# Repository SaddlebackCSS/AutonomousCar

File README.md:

# Autonomous Car for Sparkfun AVC

---
Will post more later once finals are over but I wanted to start the repo. Most information will go in the wiki, since there is a lot of  specialized terms and knowledge to the RC world. People who want to help should have a centeralized place to go to learn what they need so that this project is less intimidating to people with no prior knowledge of RC or robotics.
</br> [Read about last years contest](avc.sparkfun.com/2015)
</br> [Some pictures and info from last year on HackaDay](hackaday.io/project/6404/logs)
</br> [Video recap of last year on youtube](www.youtube.com/watch?v=tZ3fpZFWHDM)
</br> [Youtube preview of last years course, for an idea of whats involved](www.youtube.com/watch?v=ZOcVDljZUFs)

#### What we can learn from this project:
  * Microcontroller programming (aruindo, etc)
  * Embedded Computers (single board computers like the pi)
  * Signals and Controls
  * Sensor Fusion
  * Hardware design and prototyping
  * Assembly Language - I don't know it but if you do then its a great opportunity to flex your knowledge!
  * AI - probably very crude but we can see
  * Computer Vision - maybe out of reach for this first year but would be awesome!
  * Working as a team and using real life engineering best practices (!)
  * An awesome trip to the competition for those who can make it!

#### Needed Knowledge (future wiki topics):
* Electrical Subsystems of a RC vehicle
  * Lipo Battery
  * Electronic Speed Controller
  * Servo
  * Receiver (or in our case a computer/microcontroller)
  * Electric Motor
    * Brushed electric motors
    * Brushless Electric Motors
  * Signals and Controls
    * Analog vs Digital
    * Pulse Width Modulations
    * I2C serial
    * SPI serial
    * Closed Loop Feedback

Obviously what you learn is really up to what you are interested in. If you could care less about hardware but want to jsut play with computer vision or someother navigation method then thats ok! If we want we could even make more than one car, and there is also a battle bot competition if some people are more interested in that.

# Find IP of beaglebone on Windows at Saddleback
- Open CMD
- Type "nslookup beaglebone". The output will look something like: 

```
Server:  dns1.saddleback.edu
Address:  10.151.253.251

Non-authoritative answer:
Name:  beaglebone.saddleback.edu
Address:  10.151.12.96
```

- Use the address associated with beaglebone.saddleback.edu with ssh on Linux/OSX or in PUTTY(installed on school computers already)

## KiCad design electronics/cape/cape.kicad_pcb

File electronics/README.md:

# Electronics Design Files

---
This folder contains design files for harware, both schematics and layout files. the were created with the open-source program [KiCad](http://kicad-pcb.org/) which is a product of FERMI labs.

</br> [Download KiCad for windows](kicad-pcb.org/download/windows/) - Also in the AUR and most linux repositories!
</br> [Contexual Electronics - Very Good YouTUbe chan with KiCad tutorials](www.youtube.com/user/contextualelectronic/playlists)
</br> [Octopart Part Finder & price Comparison](octopart.com/)
</br> [Digikey Parts Supplier](www.digikey.com)
</br> [Mouser Parts Supply](www.mouser.com/)
</br> [PCB Fabrication Price Comparison](pcbshopper.com/)

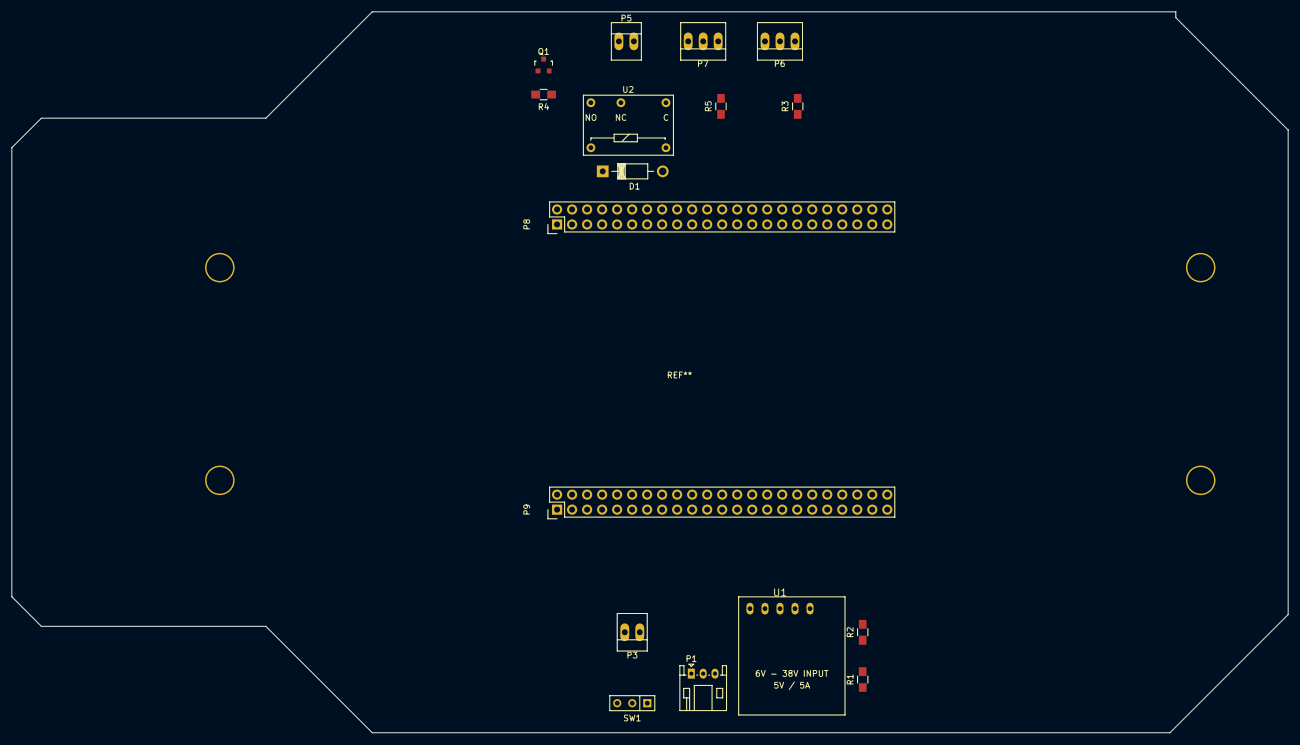
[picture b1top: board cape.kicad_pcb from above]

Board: 2 copper layers, 216.0 x 122.0 mm, 17 parts (0 on the bottom side), 16 nets, no tracks yet.

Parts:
D1: D; Diode_DO-41_SOD81_Horizontal_RM10
P1: CONN_01X03; JST_PH_S3B-PH-K_03x2.00mm_Angled
P3, P5: CONN_01X02; PINHEAD1-2
P6, P7: CONN_01X03; PINHEAD1-3
P8, P9: BeagleBone_Black_Header; Socket_BeagleBone_Black
Q1: BSS138; SOT-23
R1, R2, R5: R; R_0805_HandSoldering
R3: 1k; R_0805_HandSoldering
R4: 100k; R_0805_HandSoldering
SW1: SWITCH_INV; SW_Micro_SPST
U1: D24V50F5
U2: OMRON_RELAY_G6E; Relay_SPDS_OMRON-G6E

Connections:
+3V3: P6.2, P9.3, P9.4
+5V: D1.1, P9.5, P9.6, U2.1
ESC_SWITCH: Q1.1, R4.2
GNDD: P6.3, P7.3, P8.1, P8.2, P9.1, P9.2, P9.43, P9.44, P9.45, P9.46, Q1.2, R4.1
unnamed: D1.2, Q1.3, U2.6
unnamed: P1.1, SW1.2
unnamed: P1.3, R1.1
unnamed: P3.1, U1.3, U1.4
unnamed: P3.2, U1.5
unnamed: P5.1, U2.12
unnamed: P5.2, U2.7
unnamed: P6.1, R3.1
unnamed: P7.1, R5.2
unnamed: R1.2, R2.1, U1.1
unnamed: R2.2, SW1.3, U1.2
SYS_5V: P9.7, P9.8

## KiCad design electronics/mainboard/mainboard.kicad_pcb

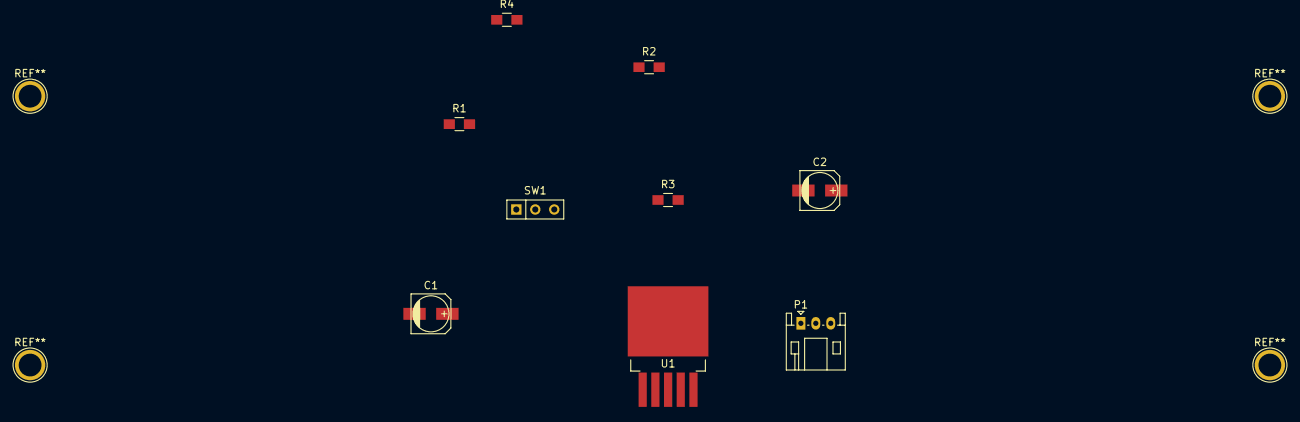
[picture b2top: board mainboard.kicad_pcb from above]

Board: 2 copper layers, 9 parts (0 on the bottom side), 6 nets, no tracks yet.

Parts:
C1: 10uF; c_elec_5x5.3
C2: 22uF; c_elec_5x5.3
P1: CONN_01X03; JST_PH_S3B-PH-K_03x2.00mm_Angled
R1, R2: 100K; R_0805_HandSoldering
R3: 33K; R_0805_HandSoldering
R4: 15K; R_0805_HandSoldering
SW1: SWITCH_INV; SW_Micro_SPST
U1: MIC29312; TO-263-5Lead

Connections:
/power supply/5V: C2.1, R2.1, U1.4
GND: C1.2, C2.2, P1.3, R3.2, R4.1, U1.3
unnamed: C1.1, R1.2, SW1.3, U1.2
unnamed: P1.1, SW1.2
unnamed: R1.1, R4.2, U1.1
unnamed: R2.2, R3.1, U1.5

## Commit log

2015-03-01 work from todays meeting
2015-03-01 Working on overlay files
2015-12-23 updated ignore file
2015-12-23 Servo/Controls Test Program
2015-12-23 started work on ESC control lib
2016-02-02 First Commit New Page
2016-02-02 config update
2016-02-02 updated about
2016-02-02 updated ignore and added images
2016-02-02 background image edited in css
2016-02-02 changed markdown to karmdown
2016-02-02 updated page titles
2016-02-02 changes to rouge for highlighting
2016-02-04 changed to platformIO and clion build env
2016-02-04 clion files
2016-02-10 cleared example posts and added post
2016-02-12 starting new blog entry
2016-02-12 working on post
2016-02-12 working
2016-03-06 add waffle.io badge
2016-04-01 add libraries for GPIO and PWM pin control
2016-04-01 add overlay for steering and script for compiling it
2016-04-01 rename steering overlay file
2016-04-02 default source of P9_16_PWM
2016-04-04 More Comments in the overlay
2016-04-04 even more comments in overlay!
2016-04-04 added electronics folder
2016-04-04 added documentation folder with BBB-SystemRefManual
2016-04-04 deleted computer specific project folders
2016-04-04 changed back to txt
2016-04-04 modified overlay for gpio relay control
2016-04-04 added pin docs
2016-04-08 add initial main that activates ESC. also added build script
2016-04-08 we can now run code that makes the car do stuff. yay. main.cpp is just a steering / motor test at this point
2016-04-09 fix some comments
2016-04-29 you should have trusted me -- courtesy of whatthecommit.com
2016-04-29 Create makefile
2016-04-29 add pthread flag
2016-04-30 Update makefile
2016-05-06 lots of stuff
2016-05-06 Set duty cycle prior to initialization. Motor move now takes whole integer
2016-05-06 fix header
2016-05-06 modify gitignore to have test binary in it
2016-05-06 MOTOR - added double tap in move()
2016-05-06 slight fixes, still doesnt work
2016-05-06 MOTOR - cleaned up move()
2016-06-05 removed old and bad schematics
2016-06-05 started kicad project with heirarchical sheets
2016-06-05 Fix formatting
2016-06-05 fix makefile! yay
2016-06-05 try to use abs before converting to unsigned int
2016-06-05 it can go backwards now
2016-06-05 Get rid of double-tap mumbo jumbo. Car now set to "Fwd / Rev" mode.
2016-06-05 remove unnecessary method
2016-06-05 testing permissions
2016-06-05 add prototype Steering class.. not ready for use, yet.
2016-06-05 fix little error and edit makefile
2016-06-05 Modify Center value for Steering and fix some messages to make them more descriptive
2016-06-05 update header to include CENTER variable
2016-06-05 steering class can steer now..
2016-06-06 changed battery to connector, added R values, and grounds
2016-06-06 power supply board added
2016-06-11 added power board to heirachry in mainboard
2016-06-11 added mounting holes in starting PCB file
2016-06-11 finished power subcircuit and made netlist
2016-06-11 modifications
2016-06-11 add pruss library to makefile
2016-06-25 added kicad lib
2016-06-26 drive in circle
2016-06-26 work on boards
